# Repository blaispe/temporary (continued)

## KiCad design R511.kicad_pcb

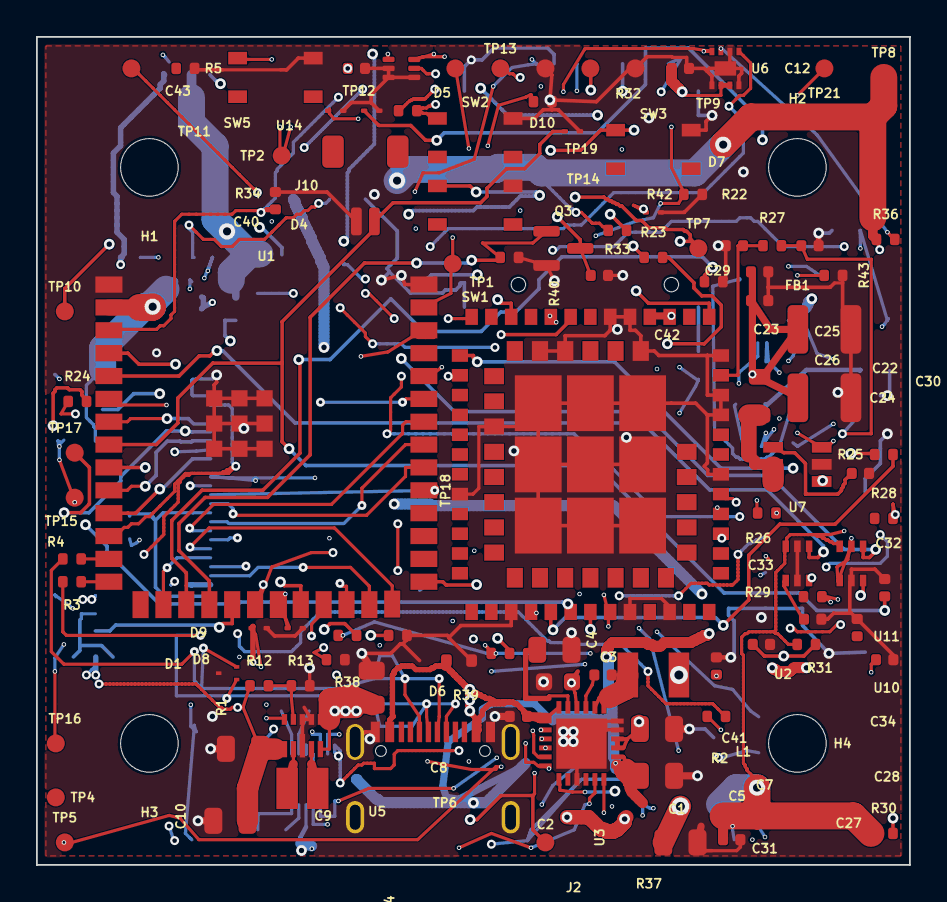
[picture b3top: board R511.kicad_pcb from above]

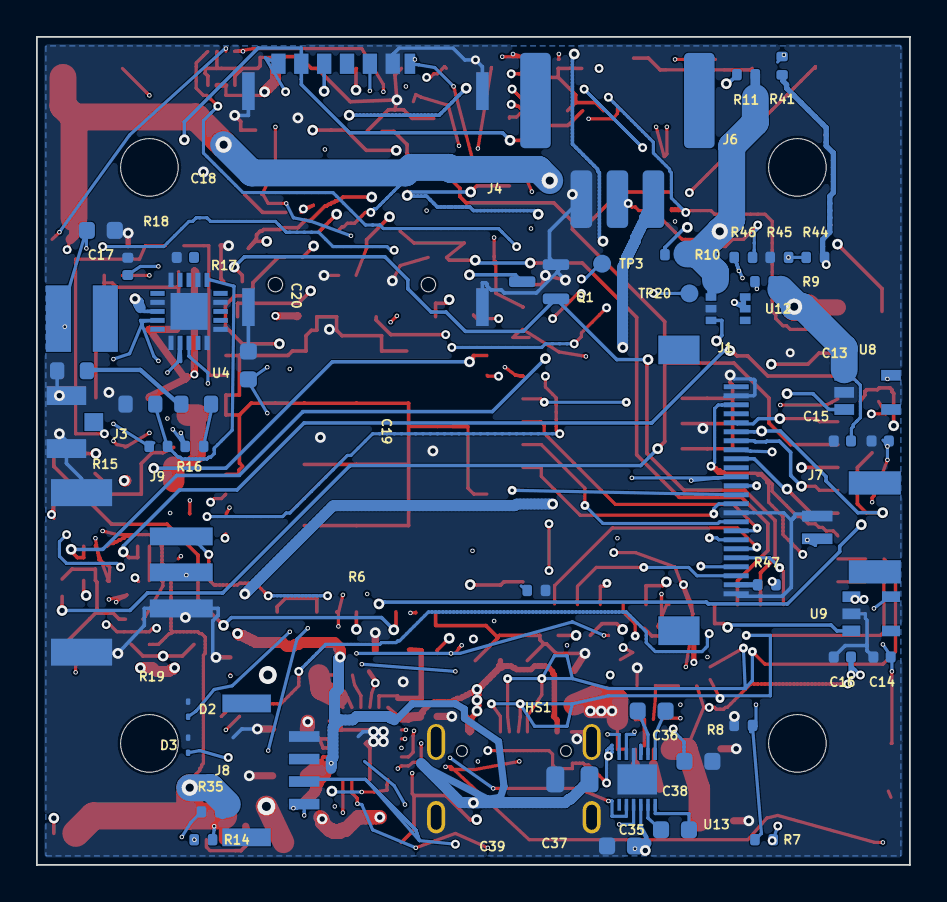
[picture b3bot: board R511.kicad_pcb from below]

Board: 6 copper layers, 48.5 x 46.0 mm, 155 parts (50 on the bottom side), 102 nets.

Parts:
C1: 47nF; C_0402_1005Metric_C1_R5_4
C2: 1uF/10V; C_0402_1005Metric_C2_R5_4
C3: 10uF/10V; C_0805_2012Metric_C3_R5_4
C4: 4.7uF/10V; C_0603_1608Metric_C4_R5_4
C5: 10uF/10V; C_0805_2012Metric_C5_R5_4
C6: 10uF/10V; C_0805_2012Metric_C6_R5_4
C7: 10uF/10V; C_0805_2012Metric_C7_R5_4
C8: 10uF; C_0805_2012Metric_C8_R5_4
C9: 22uF; C_0805_2012Metric_C9_R5_4
C10: 22uF; C_0805_2012Metric_C10_R5_4
C12: 0.1uF; C_0402_1005Metric_C12_R5_4
C13: 1uF; C_0402_1005Metric_C13_R5_4
C14: 1uF; C_0402_1005Metric_C14_R5_4
C15: 1uF; C_0402_1005Metric_C15_R5_4
C16: 1uF; C_0402_1005Metric_C16_R5_4
C17: 4.7uF; C_0603_1608Metric_C17_R5_4
C18: 10nF; C_0402_1005Metric_C18_R5_4
C19: 4.7uF; C_0603_1608Metric_C19_R5_4
C20: 100nF; C_0402_1005Metric_C20_R5_4
C22: 1nF; C_0402_1005Metric_C22_R5_4
C23: 100uF; C_1210_3225Metric_C23_R5_4
C24: 100uF; C_1210_3225Metric_C24_R5_4
C25: 1uF; C_0402_1005Metric_C25_R5_4
C26: 100nF; C_0402_1005Metric_C26_R5_4
C27: 100nF; C_0402_1005Metric_C27_R5_4
C28: 100nF; C_0402_1005Metric_C28_R5_4
C29: DNP; C_0402_1005Metric_C29_R5_4
C30: DNP; C_0402_1005Metric_C30_R5_4
C31: 1uF; C_0402_1005Metric_C31_R5_4
C32: 1uF; C_0402_1005Metric_C32_R5_4
C33: 100nF; C_0402_1005Metric_C33_R5_4
C34: 100nF; C_0402_1005Metric_C34_R5_4
C35: 2.2uF; C_0603_1608Metric_C35_R5_4
C36: 2.2uF; C_0603_1608Metric_C36_R5_4
C37: 2.2uF; C_0603_1608Metric_C37_R5_4
C38: 4.7uF; C_0603_1608Metric_C38_R5_4
C39: 22uF; C_0805_2012Metric_C39_R5_4
C40: 1uF; C_0402_1005Metric_C40_R5_4
C41: 100nF; C_0402_1005Metric_C41_R5_4
C42: 100nF; C_0402_1005Metric_C42_R5_4
C43: 100nF; C_0402_1005Metric_C43_R5_4
D1: TPD2EUSB30ADRTR; SOT-9X3-3_L1.0-W0.8-P0.35-LS1.0-BR_D1_R5_4
D2: ESD9B5.0ST5G; D_SOD-923_D2_R5_4
D3: ESD9B5.0ST5G; D_SOD-923_D3_R5_4
D4: ESD9B5.0ST5G; D_SOD-923_D4_R5_4
D5: ESD9B5.0ST5G; D_SOD-923_D5_R5_4
D6: ESD5Z5V0; D_SOD-523_D6_R5_4
D7: ESD9B5.0ST5G; D_SOD-923_D7_R5_4
D8: ESD9B5.0ST5G; D_SOD-923_D8_R5_4
D9: ESD9B5.0ST5G; D_SOD-923_D9_R5_4
D10: ESD9B5.0ST5G; D_SOD-923_D10_R5_4
FB1: BLM21PG300SN1D; L_0805_2012Metric_FB1_R5_4
H1: MOUNT_3.20_CLEARANCE; MountingHole_3.2mm_M3_H1_R5_4
H2: MOUNT_3.20_CLEARANCE; MountingHole_3.2mm_M3_H2_R5_4
H3: MOUNT_3.20_CLEARANCE; MountingHole_3.2mm_M3_H3_R5_4
H4: MOUNT_3.20_CLEARANCE; MountingHole_3.2mm_M3_H4_R5_4
HS1: OPTIONAL_THERMAL_PAD_1MM_PLUS_AL_SPREADER_23X20X1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; MECH-THERMAL-SPREADER-23X20_HS1_R5_4
J1: OV5640_FPC_24P; FPC-SMD_FH12-24S-0.5SH-55_J1_R5_4
J2: USB-C TYPE-C-31-M-31; USB-C-SMD_TYPE-C-31-M-31_J2_R5_4
J3: LTE_ANT; RF-SMD_FRF05002-JSS103M_J3_R5_4
J4: NANO_SIM; SIM-SMD_NANO-SIM6-1P-H1.37_J4_R5_4
J6: BATTERY_DURACLIK_3P; BATTERY_1x03_DURACLIK_5023520300_J6_R5_4
J7: SOLAR; CONN-SMD_SM02B-GHS-TB-LF-SN_J7_R5_4
J8: OLED_GND_3V3_SDA_SCL; CONN-SMD_4P-P1.25_SM04B-GHS-TB-LF-SN_J8_R5_4
J9: FLASH_LED; CONN-SMD_S3B-PH-SM4-TB-LF-SN_J9_R5_4
J10: SM02B-SRSS-TB_LOCAL_READ; JST_SH_SM02B-SRSS-TB_1x02-1MP_P1.00mm_Horizontal_J10_R5_4
L1: 1uH; IND-SMD_L3.2-W2.5-1_L1_R5_4
L2: 22uH; IND-SMD_L4.0-W4.0_CKCS4030-220UH-M_L2_R5_4
L4: 0.47uH; IND-SMD_L2.5-W2.0_SRP2510TMA_L4_R5_4
Q1: 2N7002; SOT-23_Q1_R5_4
Q3: 2N7002; SOT-23_Q3_R5_4
R1: 10k; R_0402_1005Metric_R1_R5_4
R2: 10k; R_0402_1005Metric_R2_R5_4
R3: 22R; R_0402_1005Metric_R3_R5_4
R4: 22R; R_0402_1005Metric_R4_R5_4
R5: 5.1k; R_0402_1005Metric_R5_R5_4
R6: 5.1k; R_0402_1005Metric_R6_R5_4
R7: 5.23k PROD_TBD_NTC; R_0402_1005Metric_R7_R5_4
R8: 30.9k PROD_TBD_NTC; R_0402_1005Metric_R8_R5_4
R9: 10k; R_0402_1005Metric_R9_R5_4
R10: 10k; R_0402_1005Metric_R10_R5_4
R11: 10k; R_0402_1005Metric_R11_R5_4
R12: 511k; R_0402_1005Metric_R12_R5_4
R13: 91k; R_0402_1005Metric_R13_R5_4
R14: 100k; R_0402_1005Metric_R14_R5_4
R15: 5.62M 1%; R_0603_1608Metric_R15_R5_4
R16: 7.32M 1%; R_0603_1608Metric_R16_R5_4
R17: 5.62M 1%; R_0603_1608Metric_R17_R5_4
R18: 5.49M 1%; R_0402_1005Metric_R18_R5_4
R19: 1.87M 1%; R_0402_1005Metric_R19_R5_4
R22: 100k; R_0402_1005Metric_R22_R5_4
R23: 22R; R_0402_1005Metric_R23_R5_4
R24: 22R; R_0402_1005Metric_R24_R5_4
R25: 22R; R_0402_1005Metric_R25_R5_4
R26: 22R; R_0402_1005Metric_R26_R5_4
R27: 0R; R_0402_1005Metric_R27_R5_4
R28: 4.7k; R_0402_1005Metric_R28_R5_4
R29: 4.7k; R_0402_1005Metric_R29_R5_4
R30: 10k; R_0402_1005Metric_R30_R5_4
R31: 10k; R_0402_1005Metric_R31_R5_4
R32: 100k; R_0402_1005Metric_R32_R5_4
R33: 10k; R_0402_1005Metric_R33_R5_4
R34: 10k; R_0402_1005Metric_R34_R5_4
R35: 4.7k; R_0402_1005Metric_R35_R5_4
R36: 4.7k; R_0402_1005Metric_R36_R5_4
R37: 4.7k; R_0402_1005Metric_R37_R5_4
R38: 4.7k; R_0402_1005Metric_R38_R5_4
R39: 100k; R_0402_1005Metric_R39_R5_4
R40: 100k; R_0402_1005Metric_R40_R5_4
R41: 100k; R_0402_1005Metric_R41_R5_4
R42: 56k; R_0402_1005Metric_R42_R5_4
R43: 100k; R_0402_1005Metric_R43_R5_4
R44: 10k EVT_ONLY; R_0402_1005Metric_R44_R5_4
R45: 10k EVT_ONLY; R_0402_1005Metric_R45_R5_4
R46: 0R PROD_NTC_LINK; R_0402_1005Metric_R46_R5_4
R47: 0R; R_0402_1005Metric_R47_R5_4
SW1: BOOT; KEY-SMD_4P-L4.2-W3.2-P2.20-LS4.6_SW1_R5_4
SW2: RESET; KEY-SMD_4P-L4.2-W3.2-P2.20-LS4.6_SW2_R5_4
SW3: FACTORY; KEY-SMD_4P-L4.2-W3.2-P2.20-LS4.6_SW3_R5_4
SW5: BQ_QON_SERVICE; KEY-SMD_4P-L4.2-W3.2-P2.20-LS4.6_SW5_R5_4
TP1: PMIC_SDA; TestPoint_Pad_D1.0mm_TP1_R5_4
TP2: PMIC_SCL; TestPoint_Pad_D1.0mm_TP2_R5_4
TP3: FUEL_ALERT_N; TestPoint_Pad_D1.0mm_TP3_R5_4
TP4: SOLAR_VBAT_OK; TestPoint_Pad_D1.0mm_TP4_R5_4
TP5: BQ_PG_N; TestPoint_Pad_D1.0mm_TP5_R5_4
TP6: BQ_STAT; TestPoint_Pad_D1.0mm_TP6_R5_4
TP7: BQ_INT_N; TestPoint_Pad_D1.0mm_TP7_R5_4
TP8: 3V3_MAIN; TestPoint_Pad_D1.0mm_TP8_R5_4
TP9: GND; TestPoint_Pad_D1.0mm_TP9_R5_4
TP10: MODEM_STATUS_1V8; TestPoint_Pad_D1.0mm_TP10_R5_4
TP11: MODEM_USB_VBUS_SERVICE; TestPoint_Pad_D1.0mm_TP11_R5_4
TP12: MODEM_USB_DP_SERVICE; TestPoint_Pad_D1.0mm_TP12_R5_4
TP13: MODEM_USB_DM_SERVICE; TestPoint_Pad_D1.0mm_TP13_R5_4
TP14: MODEM_USB_GND; TestPoint_Pad_D1.0mm_TP14_R5_4
TP15: TP_CAM_2V8; TestPoint_Pad_D1.0mm_TP15_R5_4
TP16: TP_CAM_1V5; TestPoint_Pad_D1.0mm_TP16_R5_4
TP17: TP_CAM_RESET; TestPoint_Pad_D1.0mm_TP17_R5_4
TP18: TP_CAM_XCLK; TestPoint_SMD_XCLK_0.50x0.70_NO_COURTYARD_TP18_R5_4
TP19: TP_MODEM_BOOT_CFG; TestPoint_Pad_D1.0mm_TP19_R5_4
TP20: TP_MODEM_DEBUG_TXD; TestPoint_Pad_D1.0mm_TP20_R5_4
TP21: TP_MODEM_VDD_EXT; TestPoint_Pad_D1.0mm_TP21_R5_4
U1: ESP32-S3-WROOM-1U-N16R8; WIRELM-SMD_ESP32-S3-WROOM-1U_U1_R5_4
U2: A7683E; COMM-SMD_L17.6-W15.7_A7683E_U2_R5_4
U3: BQ25601RTWR; VFQFPN-24_L4.0-W4.0-P0.50-BL-EP2.8_U3_R5_4
U4: BQ25570RGRR; VQFN-20_L3.5-W3.5-P0.50-BL-EP2.0_U4_R5_4
U5: TPS63802DLAR; VSON-10_L3.0-W2.0-P0.50-TL_U5_R5_4
U6: MAX17048G+T10; TDFN-8_L2.0-W2.0-P0.50-BL-EP1.2_U6_R5_4
U7: TPS22918DBVR; SOT-23-6_L2.9-W1.6-P0.95-LS2.8-BR_U7_R5_4
U8: TLV70028DDCR; SOT-23-5_L3.0-W1.7-P0.95-LS2.8-BR_U8_R5_4
U9: TLV70015DDCR; SOT-23-5_L2.9-W1.6-P0.95-LS2.8-BR_U9_R5_4
U10: SN74AXC1T45DCKR ESP->MODEM; SC-70-6_L2.0-W1.3-P0.65-LS2.1-BL-1_U10_R5_4
U11: SN74AXC1T45DCKR MODEM->ESP; SC-70-6_L2.0-W1.3-P0.65-LS2.1-BL-1_U11_R5_4
U12: TPS22919DCKR; SC-70-6_L2.2-W1.3-P0.65-LS2.1-BR_U12_R5_4
U13: LM2759SD/NOPB; WSON-12_L3.0-W3.0-P0.40-BL-EP_U13_R5_4
U14: TMP112AIDRLR; SOT-563_DRL0006A_TMP112_U14_R5_4

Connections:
/01_MCU_CAMERA_USB/CAM_AF_3V3: J1.23, R47.2
/01_MCU_CAMERA_USB/CAM_D0: J1.19, U1.26
/01_MCU_CAMERA_USB/CAM_D1: J1.21, U1.24
/01_MCU_CAMERA_USB/CAM_D2: J1.22, U1.25
/01_MCU_CAMERA_USB/CAM_D3: J1.20, U1.16
/01_MCU_CAMERA_USB/CAM_D4: J1.18, U1.35
/01_MCU_CAMERA_USB/CAM_D5: J1.16, U1.33
/01_MCU_CAMERA_USB/CAM_D6: J1.14, U1.32
/01_MCU_CAMERA_USB/CAM_D7: J1.12, U1.23
/01_MCU_CAMERA_USB/CAM_HREF: J1.9, U1.11
/01_MCU_CAMERA_USB/CAM_PCLK: J1.17, U1.34
/01_MCU_CAMERA_USB/CAM_PWDN_FIXED_LOW: J1.8, R1.1
/01_MCU_CAMERA_USB/CAM_RESET_CTRL: Q3.1, R40.1, U1.18
/01_MCU_CAMERA_USB/CAM_RESET_N: C42.1, J1.6, Q3.3, R2.2, TP17.1
/01_MCU_CAMERA_USB/CAM_SCCB_SCL: J1.5, R38.2, U1.7
/01_MCU_CAMERA_USB/CAM_SCCB_SDA: J1.3, R37.2, U1.12
/01_MCU_CAMERA_USB/CAM_VSYNC: J1.7, U1.10
/01_MCU_CAMERA_USB/CAM_XCLK: J1.13, TP18.1, U1.31
/01_MCU_CAMERA_USB/USB_CC1: J2.A5, R5.1
/01_MCU_CAMERA_USB/USB_CC2: J2.B5, R6.1
/01_MCU_CAMERA_USB/USB_DN: R4.2, U1.13
/01_MCU_CAMERA_USB/USB_DN_CONN: D1.2, J2.A7, J2.B7, R4.1
/01_MCU_CAMERA_USB/USB_DP: R3.2, U1.14
/01_MCU_CAMERA_USB/USB_DP_CONN: D1.1, J2.A6, J2.B6, R3.1
/02_POWER_USB_BAT/BAT_NTC: J6.2, R46.1
/02_POWER_USB_BAT/BQ_BTST: C1.1, U3.21
/02_POWER_USB_BAT/BQ_INT_N: R11.2, TP7.1, U3.7
/02_POWER_USB_BAT/BQ_PG_N: R9.2, TP5.1, U3.3
/02_POWER_USB_BAT/BQ_PMID: C3.1, U3.23
/02_POWER_USB_BAT/BQ_PSEL: R41.2, R42.1, U3.2
/02_POWER_USB_BAT/BQ_REGN: C4.1, R7.1, R41.1, R44.1, U3.22
/02_POWER_USB_BAT/BQ_STAT: R10.2, TP6.1, U3.4
/02_POWER_USB_BAT/BQ_SW: C1.2, L1.1, U3.19, U3.20
/02_POWER_USB_BAT/BQ_TS: R7.2, R8.1, R44.2, R45.1, R46.2, U3.11
/02_POWER_USB_BAT/FUEL_ALERT_N: TP3.1, U6.5
/02_POWER_USB_BAT/SYS: C5.1, C6.1, C8.1, L1.2, U3.15, U3.16, U5.1, U5.10
/02_POWER_USB_BAT/TPS_FB: R12.2, R13.1, U5.4
/02_POWER_USB_BAT/TPS_L1: L4.1, U5.9
/02_POWER_USB_BAT/TPS_L2: L4.2, U5.7
/02_POWER_USB_BAT/TPS_PG: R14.2, U5.5
/3V3_MAIN: C9.1, C10.1, C15.1, C16.1, C31.1, C43.1, R9.1, R10.1, R11.1, R12.1, R14.1, R30.1, R31.1, R33.1, R34.1, R35.1, R36.1, R47.1, TP8.1, U1.2, U5.6, U8.1, U9.1, U10.6, U11.6, U12.1, U14.5
/03_SOLAR_HARVESTER/BQ25570_LBOOST: L2.2, U4.20
/03_SOLAR_HARVESTER/BQ25570_OK_HYST: R18.2, R19.2, U4.10
/03_SOLAR_HARVESTER/BQ25570_OK_PROG: R17.1, R18.1, U4.11
/03_SOLAR_HARVESTER/BQ25570_VBAT_OV: R15.1, R16.2, U4.7
/03_SOLAR_HARVESTER/BQ25570_VRDIV: R16.1, R19.1, U4.8
/03_SOLAR_HARVESTER/BQ25570_VREF: C18.1, U4.4
/03_SOLAR_HARVESTER/BQ25570_VSTOR: C19.1, C20.1, U4.3, U4.19
/03_SOLAR_HARVESTER/SOLAR_POS: C17.1, J7.1, L2.1, U4.2
/03_SOLAR_HARVESTER/SOLAR_VBAT_OK: TP4.1, U4.13
/04_LTE_SIM_RF/LTE_ANT_MODULE: C29.1, R27.1, U2.32
/04_LTE_SIM_RF/LTE_ANT_UFL: C30.1, J3.1, R27.2
/04_LTE_SIM_RF/MODEM_1V8: C27.1, C28.1, TP21.1, U2.40, U10.1, U11.1, U11.5
/04_LTE_SIM_RF/MODEM_BOOT_CFG: TP19.1, U2.82
/04_LTE_SIM_RF/MODEM_DEBUG_TXD: TP20.1, U2.85
/04_LTE_SIM_RF/MODEM_LOAD_CT: C22.1, U7.4
/04_LTE_SIM_RF/MODEM_PWRKEY_N: Q1.3, U2.39
/04_LTE_SIM_RF/MODEM_RX_1V8: U2.2, U10.3
/04_LTE_SIM_RF/MODEM_STATUS_1V8: TP10.1, U2.42
/04_LTE_SIM_RF/MODEM_TX_1V8: U2.1, U11.3
/04_LTE_SIM_RF/MODEM_USB_DM_SERVICE: TP13.1, U2.26
/04_LTE_SIM_RF/MODEM_USB_DP_SERVICE: TP12.1, U2.25
/04_LTE_SIM_RF/MODEM_USB_VBUS_SERVICE: TP11.1, U2.24
/04_LTE_SIM_RF/MODEM_VBAT: C23.1, C24.1, C25.1, C26.1, FB1.2, U2.34, U2.35
/04_LTE_SIM_RF/MODEM_VBAT_SW: FB1.1, U7.5, U7.6
/04_LTE_SIM_RF/SIM_CLK: D3.1, J4.C3, R24.1
/04_LTE_SIM_RF/SIM_CLK_MODEM: R24.2, U2.16
/04_LTE_SIM_RF/SIM_DATA: D4.1, J4.C7, R25.1
/04_LTE_SIM_RF/SIM_DATA_MODEM: R25.2, U2.15
/04_LTE_SIM_RF/SIM_DET: D5.1, J4.CD, R26.1
/04_LTE_SIM_RF/SIM_DET_MODEM: R26.2, U2.14
/04_LTE_SIM_RF/SIM_RST: D2.1, J4.C2, R23.1
/04_LTE_SIM_RF/SIM_RST_MODEM: R23.2, U2.17
/04_LTE_SIM_RF/SIM_VDD: C41.1, J4.C1, U2.18
/05_LOCAL_UI_OLED_BUTTONS/3V3_OLED_SW: C32.1, D9.1, J8.2, R28.1, R29.1, U12.5, U12.6
/06_FLASH_ILLUMINATION/FLASH_C1N: C35.2, U13.12
/06_FLASH_ILLUMINATION/FLASH_C1P: C35.1, U13.11
/06_FLASH_ILLUMINATION/FLASH_C2N: C36.2, U13.1
/06_FLASH_ILLUMINATION/FLASH_C2P: C36.1, U13.2
/06_FLASH_ILLUMINATION/FLASH_LED_MINUS: J9.2, U13.6
/06_FLASH_ILLUMINATION/FLASH_LED_PLUS: C38.1, J9.1, U13.3
/BAT_PROTECTED: C7.1, C12.1, C37.1, C39.1, J6.1, U3.13, U3.14, U4.18, U6.2, U6.3, U7.1, U13.10
/BOOT_GPIO0: R33.2, SW1.1, U1.27
/BQ_QON_N: SW5.1, U3.12
/CAM_1V5: C14.1, J1.10, TP16.1, U9.5
/CAM_2V8: C13.1, J1.4, J1.11, R2.1, R37.1, R38.1, TP15.1, U8.5
/CAM_PWR_EN: R39.1, U1.19, U8.3, U9.3
/ESP_EN: C40.1, R34.2, SW2.1, U1.3
/FACTORY_N: C34.1, R31.2, SW3.1, U1.9
/FLASH_STROBE: R32.1, U1.36, U13.7
/GND: C2.2, C3.2, C4.2, C5.2, C6.2, C7.2, C8.2, C9.2, C10.2, C12.2, C13.2, C14.2, C15.2, C16.2, C17.2, C18.2, C19.2, C20.2, C22.2, C23.2, C24.2, C25.2, C26.2, C27.2, C28.2, C29.2, C30.2, C31.2, C32.2, C33.2, C34.2, C37.2, C38.2, C39.2, C40.2, C41.2, C42.2, C43.2, D1.3, D2.2, D3.2, D4.2, D5.2, D6.2, D7.2, D8.2, D9.2, D10.2, J1.2, J1.15, J1.24, J2.1, J2.A1, J2.A12, J3.2, J3.3, J4.1, J4.2, J4.3, J4.4, J4.C5, J6.3, J7.2, J8.1, J9.0, J9.3, J10.2, Q1.2, Q3.2, R1.2, R5.2, R6.2, R8.2, R13.2, R15.2, R17.2, R22.2, R32.2, R39.2, R40.2, R42.2, R43.2, R45.2, SW1.2, SW2.2, SW3.2, SW5.2, TP9.1, TP14.1, U1.1, U1.40, U1.41, U2.8, U2.13, U2.19, U2.21, U2.27, U2.30, U2.31, U2.33, U2.36, U2.37, U2.45, U2.63, U2.66, U2.67, U2.69, U2.70, U2.71, U2.72, U2.73, U2.74, U2.75, U2.76, U2.77, U3.9, U3.17, U3.18, U3.25, U4.1, U4.5, U4.6, U4.9, U4.12, U4.15, U4.17, U4.21, U5.2, U5.3, U5.8, U6.1, U6.4, U6.6, U6.9, U7.2, U8.2, U9.2, U10.2, U10.5, U11.2, U12.2, U13.4, U13.13, U14.2, U14.3, U14.4
/LOCAL_READ_N: C33.1, D10.1, J10.1, R30.2, U1.8
/LTE_UART_ESP_RX: U1.4, U11.4
/LTE_UART_ESP_TX: U1.5, U10.4
/MODEM_PWRKEY: Q1.1, R22.1, U1.17
/MODEM_PWR_EN: R43.1, U1.6, U7.3, U13.5
/OLED_PWR_EN: U1.22, U12.3
/OLED_SCL: D8.1, J8.4, R29.2, U1.21
/OLED_SDA: D7.1, J8.3, R28.2, U1.20
/PMIC_SCL: R36.2, TP2.1, U1.38, U3.5, U6.7, U13.9, U14.1
/PMIC_SDA: R35.2, TP1.1, U1.39, U3.6, U6.8, U13.8, U14.6
/VBUS_USB: C2.1, D6.1, J2.A4, J2.A9, U3.1, U3.24
